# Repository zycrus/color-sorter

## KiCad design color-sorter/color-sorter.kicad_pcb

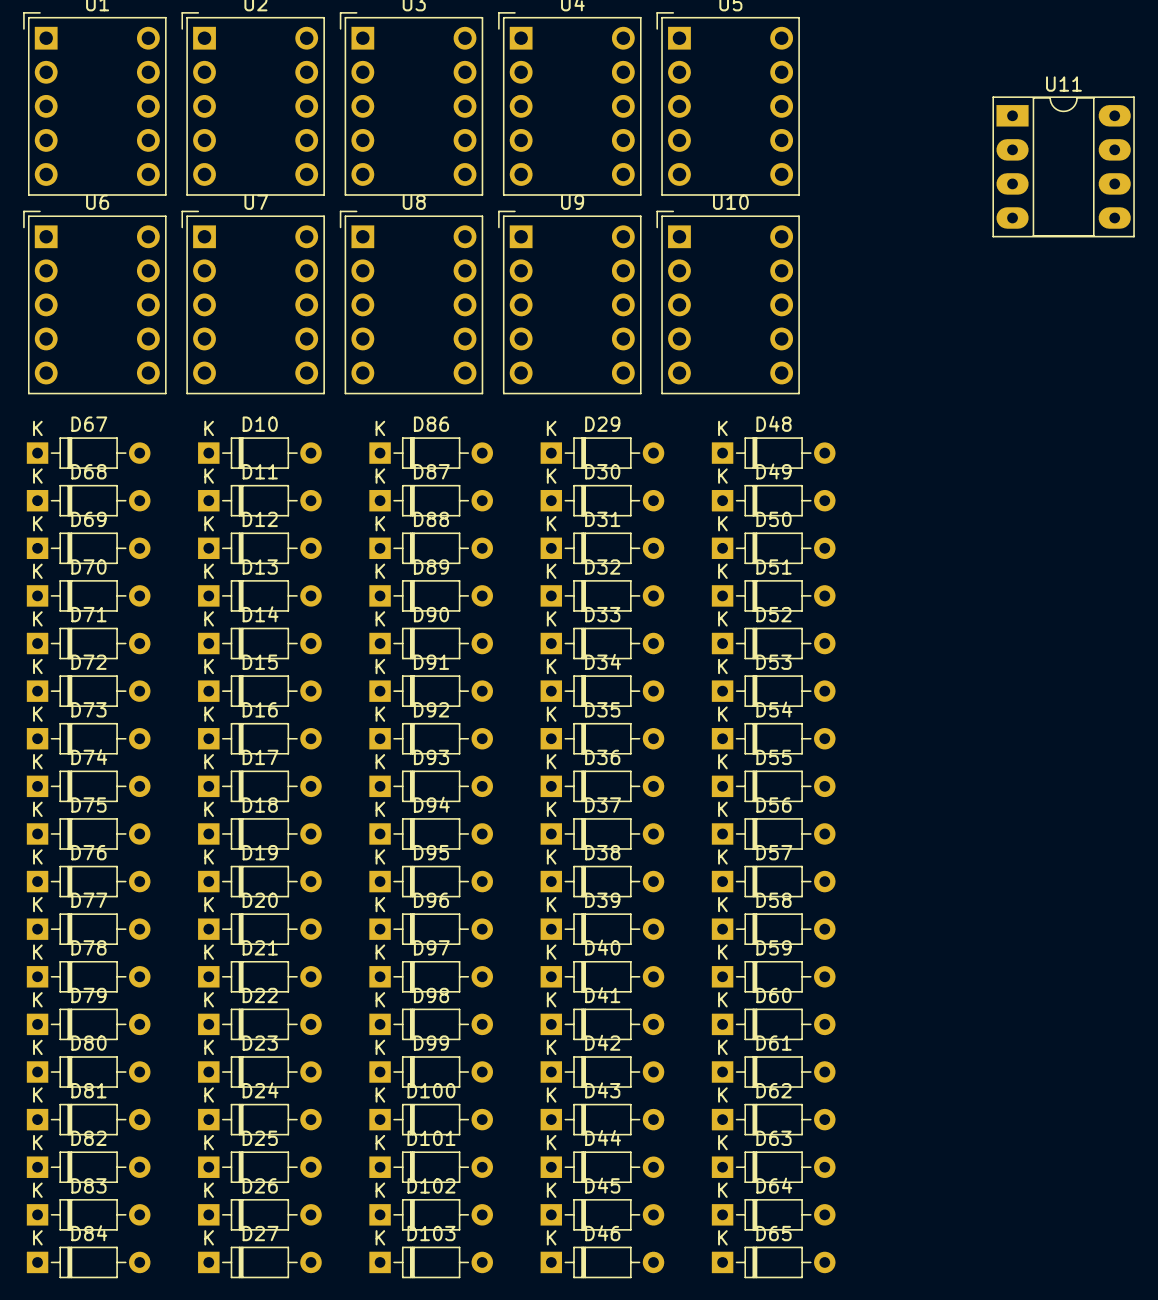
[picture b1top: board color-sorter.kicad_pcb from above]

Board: 2 copper layers, 101 parts (0 on the bottom side), 21 nets, no tracks yet.

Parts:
D10, D11, D12, D13, D14, D15, D16, D17, D18, D19, D20, D21, D22, D23, D24, D25, D26, D27, D29, D30, D31, D32, D33, D34, D35, D36, D37, D38, D39, D40, D41, D42, D43, D44, D45, D46, D48, D49, D50, D51, D52, D53, D54, D55, D56, D57, D58, D59, D60, D61, D62, D63, D64, D65, D67, D68, D69, D70, D71, D72, D73, D74, D75, D76, D77, D78, D79, D80, D81, D82, D83, D84, D86, D87, D88, D89, D90, D91, D92, D93, D94, D95, D96, D97, D98, D99, D100, D101, D102, D103: 1N4148; D_DO-35_SOD27_P7.62mm_Horizontal
U1, U2, U3, U4, U5, U6, U7, U8, U9, U10: SC39-11EWA; Sx39-1xxxxx
U11: LM324; DIP-8_W7.62mm_Socket_LongPads

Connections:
A: D10.1 (K), D11.1 (K), D12.1 (K), D13.1 (K), D14.1 (K), D15.1 (K), D16.1 (K), D17.1 (K), D18.1 (K), D29.1 (K), D30.1 (K), D31.1 (K), D32.1 (K), D33.1 (K), D34.1 (K), D35.1 (K), D36.1 (K), D37.1 (K), D48.1 (K), D49.1 (K), D50.1 (K), D51.1 (K), D52.1 (K), D53.1 (K), D54.1 (K), D55.1 (K), D56.1 (K), D67.1 (K), D68.1 (K), D69.1 (K), D70.1 (K), D71.1 (K), D72.1 (K), D73.1 (K), D74.1 (K), D75.1 (K), D86.1 (K), D87.1 (K), D88.1 (K), D89.1 (K), D90.1 (K), D91.1 (K), D92.1 (K), D93.1 (K), D94.1 (K)
A': D19.1 (K), D20.1 (K), D21.1 (K), D22.1 (K), D23.1 (K), D24.1 (K), D25.1 (K), D26.1 (K), D27.1 (K), D38.1 (K), D39.1 (K), D40.1 (K), D41.1 (K), D42.1 (K), D43.1 (K), D44.1 (K), D45.1 (K), D46.1 (K), D57.1 (K), D58.1 (K), D59.1 (K), D60.1 (K), D61.1 (K), D62.1 (K), D63.1 (K), D64.1 (K), D65.1 (K), D76.1 (K), D77.1 (K), D78.1 (K), D79.1 (K), D80.1 (K), D81.1 (K), D82.1 (K), D83.1 (K), D84.1 (K), D95.1 (K), D96.1 (K), D97.1 (K), D98.1 (K), D99.1 (K), D100.1 (K), D101.1 (K), D102.1 (K), D103.1 (K)
Earth: U1.3 (CC), U1.8 (CC), U2.3 (CC), U2.8 (CC), U3.3 (CC), U3.8 (CC), U4.3 (CC), U4.8 (CC), U5.3 (CC), U5.8 (CC), U6.3 (CC), U6.8 (CC), U7.3 (CC), U7.8 (CC), U8.3 (CC), U8.8 (CC), U9.3 (CC), U9.8 (CC), U10.3 (CC), U10.8 (CC)
Q1: D10.2 (A), D29.2 (A), D48.2 (A), D67.2 (A), D86.2 (A)
Q1': D19.2 (A), D38.2 (A), D57.2 (A), D76.2 (A), D95.2 (A)
Q2: D11.2 (A), D30.2 (A), D49.2 (A), D68.2 (A), D87.2 (A)
Q2': D20.2 (A), D39.2 (A), D58.2 (A), D77.2 (A), D96.2 (A)
Q3: D12.2 (A), D31.2 (A), D50.2 (A), D69.2 (A), D88.2 (A)
Q3': D21.2 (A), D40.2 (A), D59.2 (A), D78.2 (A), D97.2 (A)
Q4: D13.2 (A), D32.2 (A), D51.2 (A), D70.2 (A), D89.2 (A)
Q4': D22.2 (A), D41.2 (A), D60.2 (A), D79.2 (A), D98.2 (A)
Q5: D14.2 (A), D33.2 (A), D52.2 (A), D71.2 (A), D90.2 (A)
Q5': D23.2 (A), D42.2 (A), D61.2 (A), D80.2 (A), D99.2 (A)
Q6: D15.2 (A), D34.2 (A), D53.2 (A), D72.2 (A), D91.2 (A)
Q6': D24.2 (A), D43.2 (A), D62.2 (A), D81.2 (A), D100.2 (A)
Q7: D16.2 (A), D35.2 (A), D54.2 (A), D73.2 (A), D92.2 (A)
Q7': D25.2 (A), D44.2 (A), D63.2 (A), D82.2 (A), D101.2 (A)
Q8: D17.2 (A), D36.2 (A), D55.2 (A), D74.2 (A), D93.2 (A)
Q8': D26.2 (A), D45.2 (A), D64.2 (A), D83.2 (A), D102.2 (A)
Q9: D18.2 (A), D37.2 (A), D56.2 (A), D75.2 (A), D94.2 (A)
Q9': D27.2 (A), D46.2 (A), D65.2 (A), D84.2 (A), D103.2 (A)

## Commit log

2024-06-11 Rename Draft 1.pdf to schematics/Draft 1.pdf
2024-06-11 Rename Draft 2.pdf to schematics/Draft 2.pdf
2024-06-11 Rename Draft 3.pdf to schematics/Draft 3.pdf
2024-06-11 Rename Draft 4.pdf to schematics/Draft 4.pdf
2024-06-11 Added KiCAD Project Files
